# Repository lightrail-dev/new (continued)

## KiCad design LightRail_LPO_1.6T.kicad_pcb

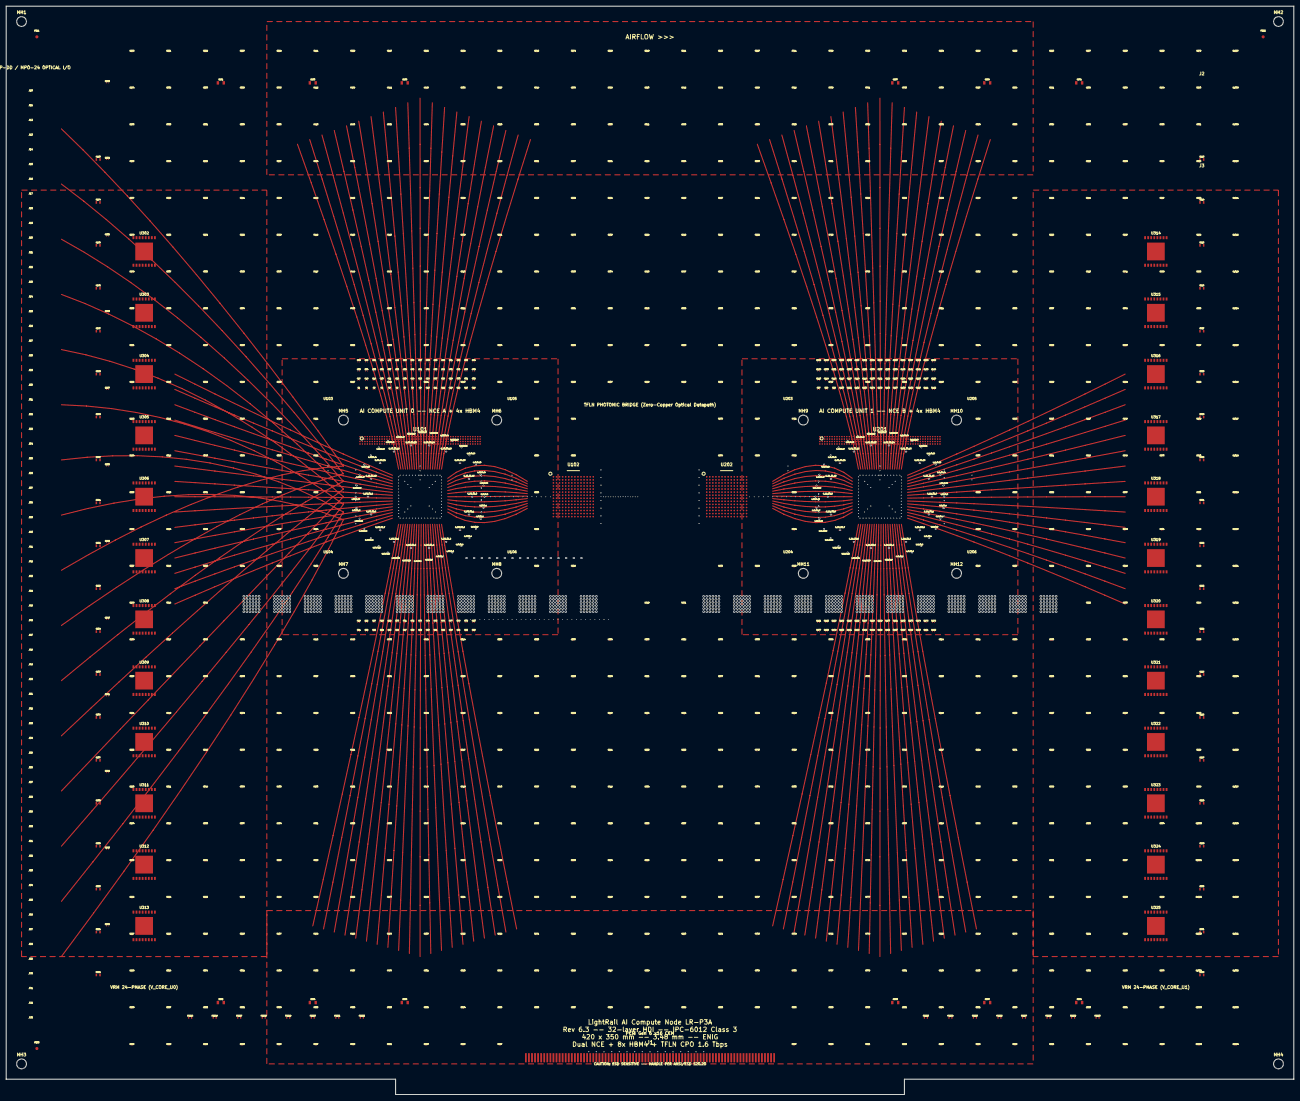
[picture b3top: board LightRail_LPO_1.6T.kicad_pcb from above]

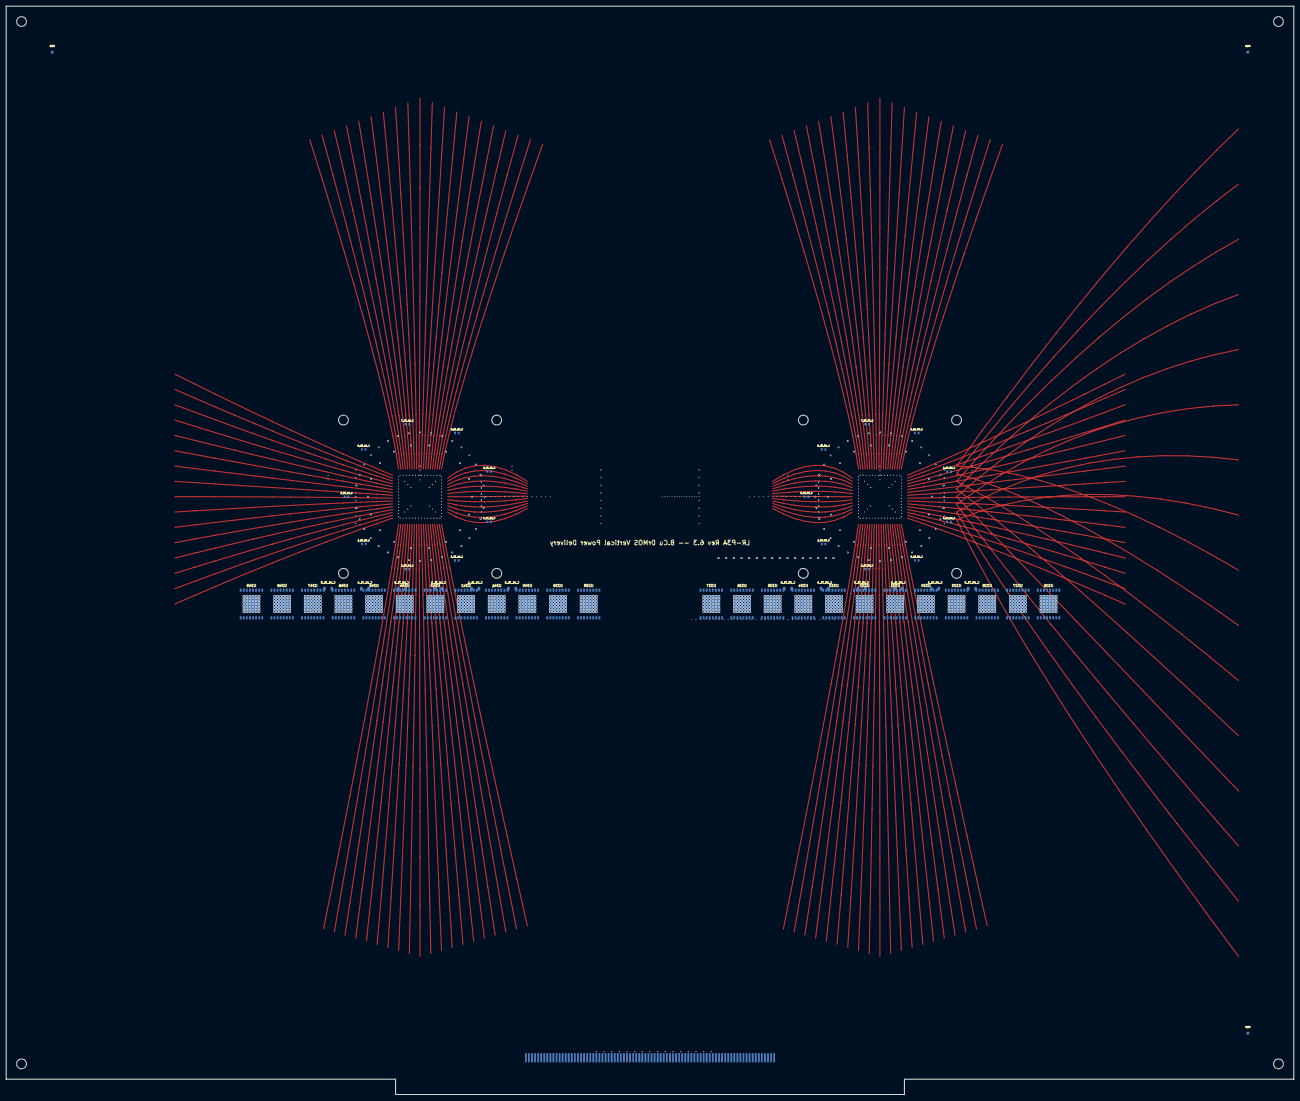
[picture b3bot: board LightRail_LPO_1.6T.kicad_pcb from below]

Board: 32 copper layers, 420.0 x 355.0 mm, 1317 parts (57 on the bottom side), 3 nets.

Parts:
C1, C2, C3, C4, C5, C6, C7, C8, C9, C10, C11, C12, C13, C14, C15, C16, C17, C18, C19, C20, C21, C22, C23, C24, C25, C26, C27, C28, C29, C30, C31, C32, C33, C34, C35, C36, C37, C38, C39, C40, C41, C42, C43, C44, C45, C46, C47, C48, C49, C50, C51, C52, C53, C54, C55, C56, C57, C58, C59, C60, C61, C62, C63, C64, C65, C66, C67, C68, C69, C70, C71, C72, C73, C74, C75, C76, C77, C78, C79, C80, C81, C82, C83, C84, C85, C86, C87, C88, C89, C90, C91, C92, C93, C94, C95, C96, C97, C98, C99, C100, C101, C102, C103, C104, C105, C106, C107, C108, C109, C110, C111, C112, C113, C114, C115, C116, C117, C118, C119, C120, C121, C122, C123, C124, C125, C126, C127, C128, C129, C130, C131, C132, C133, C134, C135, C136, C137, C138, C139, C140, C141, C142, C143, C144, C145, C146, C147, C148, C149, C150, C151, C152, C153, C154, C155, C156, C157, C158, C159, C160, C161, C162, C163, C164, C165, C166, C167, C168, C169, C170, C171, C172, C173, C174, C175, C176, C177, C178, C179, C180, C181, C182, C183, C184, C185, C186, C187, C188, C189, C190, C191, C192: 1.0x0.5; C_passive
C193, C194, C195, C196, C197, C198, C199, C200, C201, C202, C203, C204, C205, C206, C207, C208, C209, C210, C211, C212, C213, C214, C215, C216, C217, C218, C219, C220, C221, C222, C223, C224, C225, C226, C227, C228, C229, C230, C231, C232: 2.0x1.25; C_passive
C261, C262, C263, C264, C265, C266, C267, C268, C269, C270, C271, C272: 3.2x1.6; C_passive
C273, C274, C275, C276, C277, C278, C279, C280, C281, C282, C283, C284, C285, C286, C287, C288, C289, C290, C291, C292, C293, C294, C295, C296, C297, C298, C299, C300, C301, C302, C303, C304, C305, C306, C307, C308, C309, C310, C311, C312, C313, C314, C315, C316, C317, C318, C319, C320, C321, C322, C323, C324, C325, C326, C327, C328, C329, C330, C331, C332, C333, C334, C335, C336, C337, C338, C339, C340, C341, C342, C343, C344, C345, C346, C347, C348, C349, C350, C351, C352, C353, C354, C355, C356, C357, C358, C359, C360, C361, C362, C363, C364, C365, C366, C367, C368, C369, C370, C371, C372, C373, C374, C375, C376, C377, C378, C379, C380, C381, C382, C383, C384, C385, C386, C387, C388, C389, C390, C391, C392, C393, C394, C395, C396, C397, C398, C399, C400, C401, C402, C403, C404, C405, C406, C407, C408, C409, C410, C411, C412, C413, C414, C415, C416, C417, C418, C419, C420, C421, C422, C423, C424, C425, C426, C427, C428, C429, C430, C431, C432, C433, C434, C435, C436, C437, C438, C439, C440, C441, C442, C443, C444, C445, C446, C447, C448, C449, C450, C451, C452, C453, C454, C455, C456, C457, C458, C459, C460, C461, C462, C463, C464, C465, C466, C467, C468, C469, C470, C471, C472, C473, C474, C475, C476, C477, C478, C479, C480, C481, C482, C483, C484, C485, C486, C487, C488, C489, C490, C491, C492, C493, C494, C495, C496, C497, C498, C499, C500, C501, C502, C503, C504, C505, C506, C507, C508, C509, C510, C511, C512, C513, C514, C515, C516, C517, C518, C519, C520, C521, C522, C523, C524, C525, C526, C527, C528, C529, C530, C531, C532, C533, C534, C535, C536, C537, C538, C539, C540, C541, C542, C543, C544, C545, C546, C547, C548, C549, C550, C551, C552, C553, C554, C555, C556, C557, C558, C559, C560, C561, C562, C563, C564, C565, C566, C567, C568, C569, C570, C571, C572, C573, C574, C575, C576, C577, C578, C579, C580, C581, C582, C583, C584, C585, C586, C587, C588, C589, C590, C591, C592, C593, C594, C595, C596, C597, C598, C599, C600, C601, C602, C603, C604, C605, C606, C607, C608, C609, C610, C611, C612, C613, C614, C615, C616, C617, C618, C619, C620, C621, C622, C623, C624, C625, C626, C627, C628, C629, C630, C631, C632, C633, C634, C635, C636, C637, C638, C639, C640, C641, C642, C643, C644, C645, C646, C647, C648, C649, C650, C651, C652, C653, C654, C655, C656, C657, C658, C659, C660, C661, C662, C663, C664, C665, C666, C667, C668, C669, C670, C671, C672, C673, C674, C675, C676, C677, C678, C679, C680, C681, C682, C683, C684, C685, C686, C687, C688, C689, C690, C691, C692, C693, C694, C695, C696, C697, C698, C699, C700, C701, C702, C703, C704, C705, C706, C707, C708, C709, C710, C711, C712, C713, C714, C715, C716, C717, C718, C719, C720, C721, C722, C723, C724, C725, C726, C727, C728, C729, C730, C731, C732, C733, C734, C735, C736, C737, C738, C739, C740, C741, C742, C743, C744, C745, C746, C747, C748, C749, C750, C751, C752, C753, C754, C755, C756, C757, C758, C759, C760, C761, C762, C763, C764, C765, C766, C767, C768, C769, C770, C771, C772, C773, C774, C775, C776, C777, C778, C779, C780, C781, C782, C783, C784, C785, C786, C787, C788, C789, C790, C791, C792, C793, C794, C795, C796, C797, C798, C799, C800, C801, C802, C803, C804, C805, C806, C807, C808, C809, C810, C811, C812, C813, C814, C815, C816, C817, C818, C819, C820, C821, C822, C823, C824, C825, C826, C827, C828, C829, C830, C831, C832, C833, C834, C835, C836, C837, C838, C839, C840, C841, C842, C843, C844, C845, C846, C847, C848, C849, C850, C851, C852, C853, C854, C855, C856, C857, C858, C859, C860, C861, C862, C863, C864, C865, C866, C867, C868, C869, C870, C871, C872, C873, C874, C875, C876, C877, C878, C879, C880, C881, C882, C883, C884, C885, C886, C887, C888, C889, C890, C891, C892, C893, C894, C895, C896, C897, C898, C899, C900, C901, C902, C903, C904, C905, C906, C907, C908, C909, C910, C911, C912, C913, C914, C915, C916, C917, C918, C919, C920, C921, C922, C923, C924, C925, C926, C927, C928, C929, C930, C931, C932, C933, C934, C935, C936, C937, C938, C939, C940, C941, C942, C943, C944, C945, C946, C947, C948, C949, C950, C951, C952, C953, C954, C955, C956, C957, C958, C959, C960, C961, C962, C963, C964, C965, C966, C967, C968, C969, C970, C971, C972, C973, C974, C975, C976, C977, C978, C979, C980, C981, C982, C983, C984, C985, C986, C987, C988, C989, C990, C991, C992, C993, C994, C995, C996, C997, C998, C999, C1000, C1001, C1002, C1003, C1004, C1005, C1006, C1007, C1008, C1009, C1010, C1011, C1012, C1013, C1014, C1015, C1016, C1017, C1018, C1019, C1020, C1021, C1022, C1023, C1024, C1025, C1026, C1027, C1028, C1029, C1030, C1031, C1032, C1033, C1034: 0.6x0.3; C_passive
C_U0_T1_0, C_U0_T1_1, C_U0_T1_2, C_U0_T1_3, C_U0_T1_4, C_U0_T1_5, C_U1_T1_0, C_U1_T1_1, C_U1_T1_2, C_U1_T1_3, C_U1_T1_4, C_U1_T1_5: 100uF_10V; C_Tantalum_3528
C_U0_T2_0, C_U0_T2_1, C_U0_T2_2, C_U0_T2_3, C_U0_T2_4, C_U0_T2_5, C_U0_T2_6, C_U0_T2_7, C_U0_T2_8, C_U1_T2_0, C_U1_T2_1, C_U1_T2_2, C_U1_T2_3, C_U1_T2_4, C_U1_T2_5, C_U1_T2_6, C_U1_T2_7, C_U1_T2_8: 10uF; C_0805
C_U0_T3_0, C_U0_T3_1, C_U0_T3_2, C_U0_T3_3, C_U0_T3_4, C_U0_T3_5, C_U0_T3_6, C_U0_T3_7, C_U0_T3_8, C_U0_T3_9, C_U0_T3_10, C_U0_T3_11, C_U0_T3_12, C_U0_T3_13, C_U0_T3_14, C_U0_T3_15, C_U0_T3_16, C_U0_T3_17, C_U1_T3_0, C_U1_T3_1, C_U1_T3_2, C_U1_T3_3, C_U1_T3_4, C_U1_T3_5, C_U1_T3_6, C_U1_T3_7, C_U1_T3_8, C_U1_T3_9, C_U1_T3_10, C_U1_T3_11, C_U1_T3_12, C_U1_T3_13, C_U1_T3_14, C_U1_T3_15, C_U1_T3_16, C_U1_T3_17: 1uF; C_0402
C_U0_T4_0, C_U0_T4_1, C_U0_T4_2, C_U0_T4_3, C_U0_T4_4, C_U0_T4_5, C_U0_T4_6, C_U0_T4_7, C_U0_T4_8, C_U0_T4_9, C_U0_T4_10, C_U0_T4_11, C_U0_T4_12, C_U0_T4_13, C_U0_T4_14, C_U0_T4_15, C_U0_T4_16, C_U0_T4_17, C_U0_T4_18, C_U0_T4_19, C_U0_T4_20, C_U0_T4_21, C_U0_T4_22, C_U0_T4_23, C_U0_T4_24, C_U0_T4_25, C_U0_T4_26, C_U0_T4_27, C_U0_T4_28, C_U0_T4_29, C_U0_T4_30, C_U0_T4_31, C_U0_T4_32, C_U0_T4_33, C_U0_T4_34, C_U0_T4_35, C_U1_T4_0, C_U1_T4_1, C_U1_T4_2, C_U1_T4_3, C_U1_T4_4, C_U1_T4_5, C_U1_T4_6, C_U1_T4_7, C_U1_T4_8, C_U1_T4_9, C_U1_T4_10, C_U1_T4_11, C_U1_T4_12, C_U1_T4_13, C_U1_T4_14, C_U1_T4_15, C_U1_T4_16, C_U1_T4_17, C_U1_T4_18, C_U1_T4_19, C_U1_T4_20, C_U1_T4_21, C_U1_T4_22, C_U1_T4_23, C_U1_T4_24, C_U1_T4_25, C_U1_T4_26, C_U1_T4_27, C_U1_T4_28, C_U1_T4_29, C_U1_T4_30, C_U1_T4_31, C_U1_T4_32, C_U1_T4_33, C_U1_T4_34, C_U1_T4_35: 100nF; C_01005
FB245, FB246, FB247, FB248, FB249, FB250, FB251, FB252, FB253, FB254, FB255, FB256, FB257, FB258, FB259, FB260: 1.6x0.8; FB_passive
FID1, FID2, FID3, FID4, FID5, FID6: Fiducial; Fiducial_1mm_Mask2.5mm
J1: PCIe_Gen6_x16_CEM; PCIe_CEM_x16_164pin
J2, J3: 12VHPWR_600W; 12VHPWR_Molex_203713
J10, J11, J12, J13, J14, J15, J16, J17, J18, J19, J20, J21, J22, J23, J24, J25, J26, J27, J28, J29, J30, J31, J32, J33, J34, J35, J36, J37, J38, J39, J40, J41, J42, J43, J44, J45, J46, J47, J48, J49, J50, J51, J52, J53, J54, J55, J56, J57, J58, J59, J60, J61, J62, J63, J64, J65, J66, J67, J68, J69, J70, J71, J72, J73: QSFP-DD; QSFP_DD_Cage
MH1, MH2, MH3, MH4, MH5, MH6, MH7, MH8, MH9, MH10, MH11, MH12: MountingHole; MountingHole_3.2mm_M3
R233, R234, R235, R236, R237, R238, R239, R240, R241, R242, R243, R244: 1.0x0.5; R_passive
U101, U201: NCE_BGA2500_HBM4; NCE_BGA2500_40x40mm
U102, U202: TFLN_PIC_8CH_200G; TFLN_PIC_17x17mm
U103, U104, U105, U106, U203, U204, U205, U206: HBM4_12Hi_48GB; HBM4_Stack_11x11mm
U302, U303, U304, U305, U306, U307, U308, U309, U310, U311, U312, U313, U314, U315, U316, U317, U318, U319, U320, U321, U322, U323, U324, U325, U326, U327, U328, U329, U330, U331, U332, U333, U334, U335, U336, U337, U338, U339, U340, U341, U342, U343, U344, U345, U346, U347, U348, U349: ISL99390; DrMOS_PowerPAK_8x8mm

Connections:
GND: C_U0_T1_0.2, C_U0_T1_1.2, C_U0_T1_2.2, C_U0_T1_3.2, C_U0_T1_4.2, C_U0_T1_5.2, C_U0_T2_0.2, C_U0_T2_1.2, C_U0_T2_2.2, C_U0_T2_3.2, C_U0_T2_4.2, C_U0_T2_5.2, C_U0_T2_6.2, C_U0_T2_7.2, C_U0_T2_8.2, C_U0_T3_0.2, C_U0_T3_1.2, C_U0_T3_2.2, C_U0_T3_3.2, C_U0_T3_4.2, C_U0_T3_5.2, C_U0_T3_6.2, C_U0_T3_7.2, C_U0_T3_8.2, C_U0_T3_9.2, C_U0_T3_10.2, C_U0_T3_11.2, C_U0_T3_12.2, C_U0_T3_13.2, C_U0_T3_14.2, C_U0_T3_15.2, C_U0_T3_16.2, C_U0_T3_17.2, C_U0_T4_0.2, C_U0_T4_1.2, C_U0_T4_2.2, C_U0_T4_3.2, C_U0_T4_4.2, C_U0_T4_5.2, C_U0_T4_6.2, C_U0_T4_7.2, C_U0_T4_8.2, C_U0_T4_9.2, C_U0_T4_10.2, C_U0_T4_11.2, C_U0_T4_12.2, C_U0_T4_13.2, C_U0_T4_14.2, C_U0_T4_15.2, C_U0_T4_16.2, C_U0_T4_17.2, C_U0_T4_18.2, C_U0_T4_19.2, C_U0_T4_20.2, C_U0_T4_21.2, C_U0_T4_22.2, C_U0_T4_23.2, C_U0_T4_24.2, C_U0_T4_25.2, C_U0_T4_26.2, C_U0_T4_27.2, C_U0_T4_28.2, C_U0_T4_29.2, C_U0_T4_30.2, C_U0_T4_31.2, C_U0_T4_32.2, C_U0_T4_33.2, C_U0_T4_34.2, C_U0_T4_35.2, C_U1_T1_0.2, C_U1_T1_1.2, C_U1_T1_2.2, C_U1_T1_3.2, C_U1_T1_4.2, C_U1_T1_5.2, C_U1_T2_0.2, C_U1_T2_1.2, C_U1_T2_2.2, C_U1_T2_3.2, C_U1_T2_4.2, C_U1_T2_5.2, C_U1_T2_6.2, C_U1_T2_7.2, C_U1_T2_8.2, C_U1_T3_0.2, C_U1_T3_1.2, C_U1_T3_2.2, C_U1_T3_3.2, C_U1_T3_4.2, C_U1_T3_5.2, C_U1_T3_6.2, C_U1_T3_7.2, C_U1_T3_8.2, C_U1_T3_9.2, C_U1_T3_10.2, C_U1_T3_11.2, C_U1_T3_12.2, C_U1_T3_13.2, C_U1_T3_14.2, C_U1_T3_15.2, C_U1_T3_16.2, C_U1_T3_17.2, C_U1_T4_0.2, C_U1_T4_1.2, C_U1_T4_2.2, C_U1_T4_3.2, C_U1_T4_4.2, C_U1_T4_5.2, C_U1_T4_6.2, C_U1_T4_7.2, C_U1_T4_8.2, C_U1_T4_9.2, C_U1_T4_10.2, C_U1_T4_11.2, C_U1_T4_12.2, C_U1_T4_13.2, C_U1_T4_14.2, C_U1_T4_15.2, C_U1_T4_16.2, C_U1_T4_17.2, C_U1_T4_18.2, C_U1_T4_19.2, C_U1_T4_20.2, C_U1_T4_21.2, C_U1_T4_22.2, C_U1_T4_23.2, C_U1_T4_24.2, C_U1_T4_25.2, C_U1_T4_26.2, C_U1_T4_27.2, C_U1_T4_28.2, C_U1_T4_29.2, C_U1_T4_30.2, C_U1_T4_31.2, C_U1_T4_32.2, C_U1_T4_33.2, C_U1_T4_34.2, C_U1_T4_35.2, J1.A1, J1.A2, J1.A3, J1.A4, J1.A5, J1.A6, J1.A7, J1.A8, J1.A9, J1.A10, J1.A11, J1.A12, J1.A13, J1.A14, J1.A15, J1.A16, J1.A17, J1.A18, J1.A19, J1.A20, J1.A21, J1.A22, J1.A23, J1.A24, J1.A25, J1.A26, J1.A27, J1.A28, J1.A29, J1.A30, J1.A31, J1.A32, J1.A33, J1.A34, J1.A35, J1.A36, J1.A37, J1.A38, J1.A39, J1.A40, J1.A41, J1.A42, J1.A43, J1.A44, J1.A45, J1.A46, J1.A47, J1.A48, J1.A49, J1.A50, J1.A51, J1.A52, J1.A53, J1.A54, J1.A55, J1.A56, J1.A57, J1.A58, J1.A59, J1.A60, J1.A61, J1.A62, J1.A63, J1.A64, J1.A65, J1.A66, J1.A67, J1.A68, J1.A69, J1.A70, J1.A71, J1.A72, J1.A73, J1.A74, J1.A75, J1.A76, J1.A77, J1.A78, J1.A79, J1.A80, J1.A81, J1.A82, J1.B1, J1.B2, J1.B3, J1.B4, J1.B5, J1.B6, J1.B7, J1.B8, J1.B9, J1.B10, J1.B11, J1.B12, J1.B13, J1.B14, J1.B15, J1.B16, J1.B17, J1.B18, J1.B19, J1.B20, J1.B21, J1.B22, J1.B23, J1.B24, J1.B25, J1.B26, J1.B27, J1.B28, J1.B29, J1.B30, J1.B31, J1.B32, J1.B33, J1.B34, J1.B35, J1.B36, J1.B37, J1.B38, J1.B39, J1.B40, J1.B41, J1.B42, J1.B43, J1.B44, J1.B45, J1.B46, J1.B47, J1.B48, J1.B49, J1.B50, J1.B51, J1.B52, J1.B53, J1.B54, J1.B55, J1.B56, J1.B57, J1.B58, J1.B59, J1.B60, J1.B61, J1.B62, J1.B63, J1.B64, J1.B65, J1.B66, J1.B67, J1.B68, J1.B69, J1.B70, J1.B71, J1.B72, J1.B73, J1.B74, J1.B75, J1.B76, J1.B77, J1.B78, J1.B79, J1.B80, J1.B81, J1.B82, U101.A1, U101.A3, U101.A5, U101.A7, U101.A9, U101.A11, U101.A13, U101.A15, U101.A17, U101.A19, U101.A21, U101.A23, U101.A25, U101.A27, U101.A29, U101.A31, U101.A33, U101.A35, U101.A37, U101.A39, U101.A41, U101.A43, U101.A45, U101.A47, U101.A49, U101.B2, U101.B4, U101.B6, U101.B8, U101.B10, U101.B12, U101.B14, U101.B16, U101.B18, U101.B20, U101.B22, U101.B24, U101.B26, U101.B28, U101.B30, U101.B32, U101.B34, U101.B36, U101.B38, U101.B40, U101.B42, U101.B44, U101.B46, U101.B48, U101.B50, U101.C1, U101.C3, U101.C5, U101.C7, U101.C9, U101.C11, U101.C13, U101.C15, U101.C17, U101.C19, U101.C21, U101.C23, U101.C25, U101.C27, U101.C29, U101.C31, U101.C33, U101.C35, U101.C37, U101.C39, U101.C41, U101.C43, U101.C45, U101.C47, U101.C49, U101.D2, U101.D4, U101.D5, U101.D6, U101.D7, U101.D8, U101.D9, U101.D10, U101.D11, U101.D12, U101.D13, U101.D14, U101.D15, U101.D16, U101.D17, U101.D18, U101.D19, U101.D20, U101.D21, U101.D22, U101.D23, U101.D24, U101.D25, U101.D26, U101.D27, U101.D28, U101.D29, U101.D30, U101.D31, U101.D32, U101.D33, U101.D34, U101.D35, U101.D36, U101.D37, U101.D38, U101.D39, U101.D40, U101.D41, U101.D42, U101.D43, U101.D44, U101.D45, U101.D46, U101.D47, U101.D48, U101.D50, U102.A1, U102.A2, U102.A3, U102.A4, U102.A5, U102.A6, U102.A7, U102.A8, U102.A9, U102.A10, U102.A11, U102.A12, U102.A13, U102.A14, U102.B1, U102.B2, U102.B3, U102.B4, U102.B5, U102.B6, U102.B7, U102.B8, U102.B9, U102.B10, U102.B11, U102.B12, U102.B13, U102.B14, U102.C1, U102.C2, U102.C3, U102.C4, U102.C5, U102.C6, U102.C7, U102.C8, U102.C9, U102.C10, U102.C11, U102.C12, U102.C13, U102.C14, U102.D1, U102.D2, U102.D3, U102.D4, U102.D5, U102.D6, U102.D7, U102.D8, U102.D9, U102.D10, U102.D11, U102.D12, U102.D13, U102.D14, U102.E1, U102.E2, U102.E3, U102.E4, U102.E5, U102.E6, U102.E7, U102.E8, U102.E9, U102.E10, U102.E11, U102.E12, U102.E13, U102.E14, U102.F1, U102.F2, U102.F3, U102.F4, U102.F5, U102.F6, U102.F7, U102.F8, U102.F9, U102.F10, U102.F11, U102.F12, U102.F13, U102.F14, U102.G1, U102.G2, U102.G3, U102.G4, U102.G5, U102.G6, U102.G7, U102.G8, U102.G9, U102.G10, U102.G11, U102.G12, U102.G13, U102.G14, U102.H1, U102.H2, U102.H3, U102.H4, U102.H5, U102.H6, U102.H7, U102.H8, U102.H9, U102.H10, U102.H11, U102.H12, U102.H13, U102.H14, U102.I1, U102.I2, U102.I3, U102.I4, U102.I5, U102.I6, U102.I7, U102.I8, U102.I9, U102.I10, U102.I11, U102.I12, U102.I13, U102.I14, U102.J1, U102.J2, U102.J3, U102.J4, U102.J5, U102.J6, U102.J7, U102.J8, U102.J9, U102.J10, U102.J11, U102.J12, U102.J13, U102.J14, U102.K1, U102.K2, U102.K3, U102.K4, U102.K5, U102.K6, U102.K7, U102.K8, U102.K9, U102.K10, U102.K11, U102.K12, U102.K13, U102.K14, U102.L1, U102.L2, U102.L3, U102.L4, U102.L5, U102.L6, U102.L7, U102.L8, U102.L9, U102.L10, U102.L11, U102.L12, U102.L13, U102.L14, U102.M1, U102.M2, U102.M3, U102.M4, U102.M5, U102.M6, U102.M7, U102.M8, U102.M9, U102.M10, U102.M11, U102.M12, U102.M13, U102.M14, U102.N1, U102.N2, U102.N3, U102.N4, U102.N5, U102.N6, U102.N7, U102.N8, U102.N9, U102.N10, U102.N11, U102.N12, U102.N13, U102.N14, U201.A1, U201.A3, U201.A5, U201.A7, U201.A9, U201.A11, U201.A13, U201.A15, U201.A17, U201.A19, U201.A21, U201.A23, U201.A25, U201.A27, U201.A29, U201.A31, U201.A33, U201.A35, U201.A37, U201.A39, U201.A41, U201.A43, U201.A45, U201.A47, U201.A49, U201.B2, U201.B4, U201.B6, U201.B8, U201.B10, U201.B12, U201.B14, U201.B16, U201.B18, U201.B20, U201.B22, U201.B24, U201.B26, U201.B28, U201.B30, U201.B32, U201.B34, U201.B36, U201.B38, U201.B40, U201.B42, U201.B44, U201.B46, U201.B48, U201.B50, U201.C1, U201.C3, U201.C5, U201.C7, U201.C9, U201.C11, U201.C13, U201.C15, U201.C17, U201.C19, U201.C21, U201.C23, U201.C25, U201.C27, U201.C29, U201.C31, U201.C33, U201.C35, U201.C37, U201.C39, U201.C41, U201.C43, U201.C45, U201.C47, U201.C49, U201.D2, U201.D4, U201.D5, U201.D6, U201.D7, U201.D8, U201.D9, U201.D10, U201.D11, U201.D12, U201.D13, U201.D14, U201.D15, U201.D16, U201.D17, U201.D18, U201.D19, U201.D20, U201.D21, U201.D22, U201.D23, U201.D24, U201.D25, U201.D26, U201.D27, U201.D28, U201.D29, U201.D30, U201.D31, U201.D32, U201.D33, U201.D34, U201.D35, U201.D36, U201.D37, U201.D38, U201.D39, U201.D40, U201.D41, U201.D42, U201.D43, U201.D44, U201.D45, U201.D46, U201.D47, U201.D48, U201.D50, U202.A1, U202.A2, U202.A3, U202.A4, U202.A5, U202.A6, U202.A7, U202.A8, U202.A9, U202.A10, U202.A11, U202.A12, U202.A13, U202.A14, U202.B1, U202.B2, U202.B3, U202.B4, U202.B5, U202.B6, U202.B7, U202.B8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
V_CORE_U0: U101.A2, U101.A4, U101.A6, U101.A8, U101.A10, U101.A12, U101.A14, U101.A16, U101.A18, U101.A20, U101.A22, U101.A24, U101.A26, U101.A28, U101.A30, U101.A32, U101.A34, U101.A36, U101.A38, U101.A40, U101.A42, U101.A44, U101.A46, U101.A48, U101.A50, U101.B1, U101.B3, U101.B5, U101.B7, U101.B9, U101.B11, U101.B13, U101.B15, U101.B17, U101.B19, U101.B21, U101.B23, U101.B25, U101.B27, U101.B29, U101.B31, U101.B33, U101.B35, U101.B37, U101.B39, U101.B41, U101.B43, U101.B45, U101.B47, U101.B49, U101.C2, U101.C4, U101.C6, U101.C8, U101.C10, U101.C12, U101.C14, U101.C16, U101.C18, U101.C20, U101.C22, U101.C24, U101.C26, U101.C28, U101.C30, U101.C32, U101.C34, U101.C36, U101.C38, U101.C40, U101.C42, U101.C44, U101.C46, U101.C48, U101.C50, U101.D1, U101.D3, U101.D49, U302.EP, U303.EP, U304.EP, U305.EP, U306.EP, U307.EP, U308.EP, U309.EP, U310.EP, U311.EP, U312.EP, U313.EP, U326.EP, U327.EP, U328.EP, U329.EP, U330.EP, U331.EP, U332.EP, U333.EP, U334.EP, U335.EP, U336.EP, U337.EP
V_CORE_U1: U201.A2, U201.A4, U201.A6, U201.A8, U201.A10, U201.A12, U201.A14, U201.A16, U201.A18, U201.A20, U201.A22, U201.A24, U201.A26, U201.A28, U201.A30, U201.A32, U201.A34, U201.A36, U201.A38, U201.A40, U201.A42, U201.A44, U201.A46, U201.A48, U201.A50, U201.B1, U201.B3, U201.B5, U201.B7, U201.B9, U201.B11, U201.B13, U201.B15, U201.B17, U201.B19, U201.B21, U201.B23, U201.B25, U201.B27, U201.B29, U201.B31, U201.B33, U201.B35, U201.B37, U201.B39, U201.B41, U201.B43, U201.B45, U201.B47, U201.B49, U201.C2, U201.C4, U201.C6, U201.C8, U201.C10, U201.C12, U201.C14, U201.C16, U201.C18, U201.C20, U201.C22, U201.C24, U201.C26, U201.C28, U201.C30, U201.C32, U201.C34, U201.C36, U201.C38, U201.C40, U201.C42, U201.C44, U201.C46, U201.C48, U201.C50, U201.D1, U201.D3, U201.D49, U314.EP, U315.EP, U316.EP, U317.EP, U318.EP, U319.EP, U320.EP, U321.EP, U322.EP, U323.EP, U324.EP, U325.EP, U338.EP, U339.EP, U340.EP, U341.EP, U342.EP, U343.EP, U344.EP, U345.EP, U346.EP, U347.EP, U348.EP, U349.EP

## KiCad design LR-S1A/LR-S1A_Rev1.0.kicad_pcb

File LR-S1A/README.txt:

LR-S1A 1U CPO Switch Motherboard — Rev 1.0 Manufacturing Release
================================================================

Date: 2026-04-19
Designer: LightRail AI — Design Automation
Format: KiCad 8 native (schema 20240108)
Outline: 440 x 550 mm 1U rack-mount motherboard
Stackup: 18-layer HDI (Megtron-7 / High-Tg FR-4 / Faradflex BC24)

Directory layout
----------------
  native/      KiCad 8 project (.kicad_pcb / .kicad_pro)
  gerbers/     RS-274X Gerber 27 layers (18 Cu + masks/silks/paste/fab/edge)
  drill/       Excellon 2.0 PTH + NPTH
  3d/          STEP AP242 board outline + components
  ipc2581/     IPC-2581 Rev C unified design exchange package
  pdfs/        27 per-layer PDFs (A2 landscape, with plane fill + antipads
               + characteristics + compliance summary for each layer)
  drawings/    Fab Drawing, Assembly Drawings (top + bottom), Layer Index
               — all A2 landscape, full title block, IPC-grade content
  BOM.csv      2,320-part architectural BOM (5 categories)
  *_pnp.csv    Pick-and-place CSV (both sides, mm)
  DRC_report.rpt   IPC-6012 Class 3 DRC sign-off: 0 errors

DRC: IPC-6012 Class 3 ruleset, 0 violations.

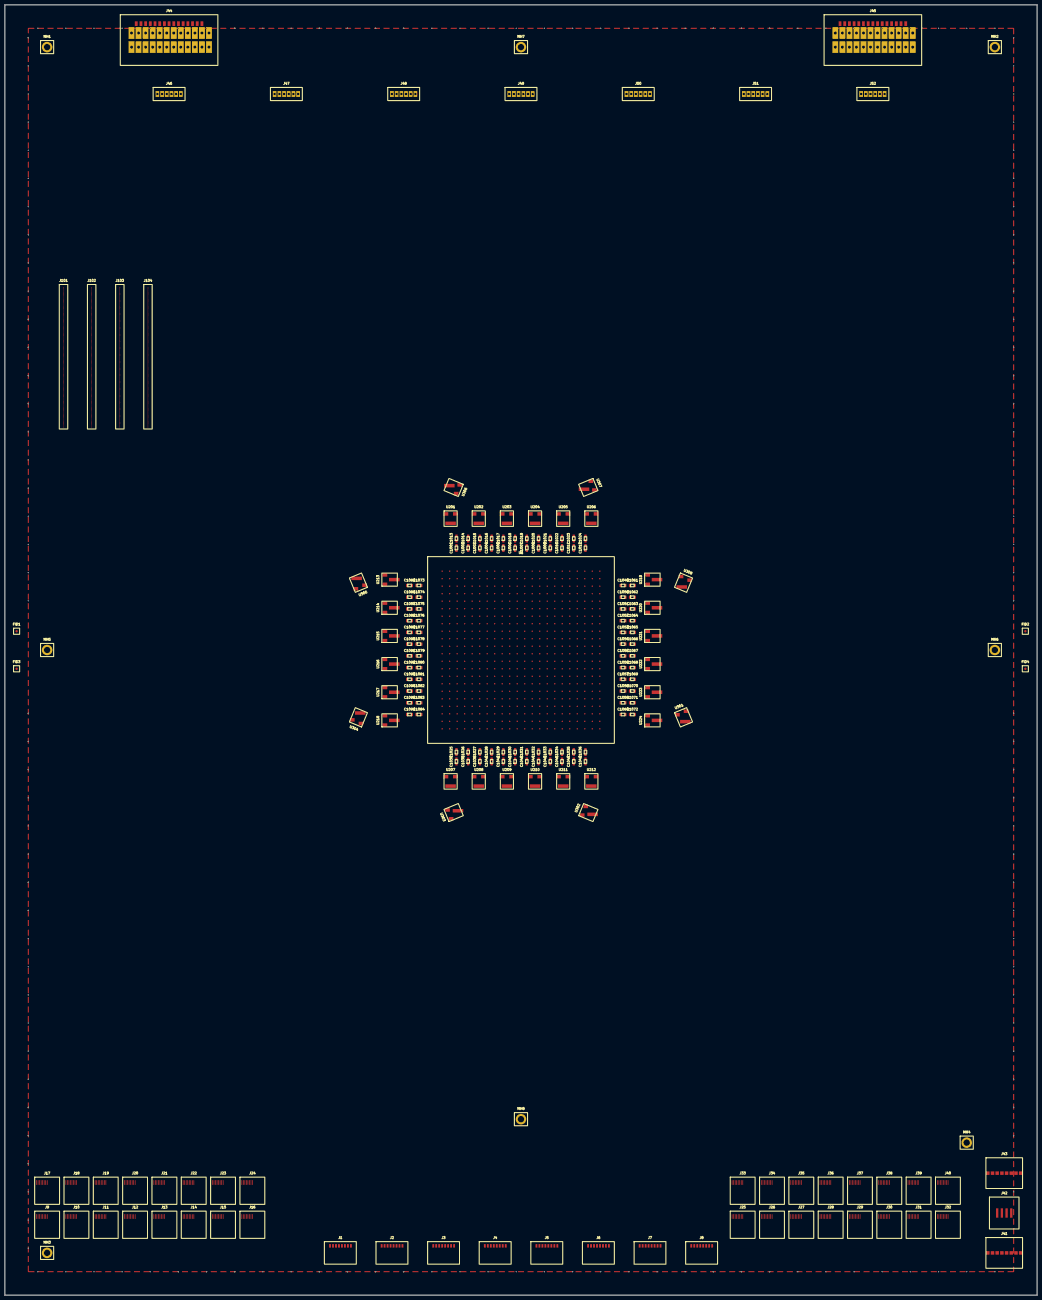
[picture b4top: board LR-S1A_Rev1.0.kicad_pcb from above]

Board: 18 copper layers, 440.0 x 550.0 mm, 197 parts (0 on the bottom side), 48 nets, no tracks yet.

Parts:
C1001, C1002, C1003, C1004, C1005, C1006, C1007, C1008, C1009, C1010, C1011, C1012, C1013, C1014, C1015, C1016, C1017, C1018, C1019, C1020, C1021, C1022, C1023, C1024, C1025, C1026, C1027, C1028, C1029, C1030, C1031, C1032, C1033, C1034, C1035, C1036, C1037, C1038, C1039, C1040, C1041, C1042, C1043, C1044, C1045, C1046, C1047, C1048, C1049, C1050, C1051, C1052, C1053, C1054, C1055, C1056, C1057, C1058, C1059, C1060, C1061, C1062, C1063, C1064, C1065, C1066, C1067, C1068, C1069, C1070, C1071, C1072, C1073, C1074, C1075, C1076, C1077, C1078, C1079, C1080, C1081, C1082, C1083, C1084, C1085, C1086, C1087, C1088, C1089, C1090, C1091, C1092, C1093, C1094, C1095, C1096: 10uF; Cap_0805_2012Metric
FID1, FID2, FID3, FID4: Fiducial 1mm/2mm; Fiducial_1mm
J1: ELSFP CW Laser Cage #1; ELSFP_Cage_SFP-DD
J2: ELSFP CW Laser Cage #2; ELSFP_Cage_SFP-DD
J3: ELSFP CW Laser Cage #3; ELSFP_Cage_SFP-DD
J4: ELSFP CW Laser Cage #4; ELSFP_Cage_SFP-DD
J5: ELSFP CW Laser Cage #5; ELSFP_Cage_SFP-DD
J6: ELSFP CW Laser Cage #6; ELSFP_Cage_SFP-DD
J7: ELSFP CW Laser Cage #7; ELSFP_Cage_SFP-DD
J8: ELSFP CW Laser Cage #8; ELSFP_Cage_SFP-DD
J9: OSFP-XD Port #1 (left lower); OSFP-XD_Cage
J10: OSFP-XD Port #2 (left lower); OSFP-XD_Cage
J11: OSFP-XD Port #3 (left lower); OSFP-XD_Cage
J12: OSFP-XD Port #4 (left lower); OSFP-XD_Cage
J13: OSFP-XD Port #5 (left lower); OSFP-XD_Cage
J14: OSFP-XD Port #6 (left lower); OSFP-XD_Cage
J15: OSFP-XD Port #7 (left lower); OSFP-XD_Cage
J16: OSFP-XD Port #8 (left lower); OSFP-XD_Cage
J17: OSFP-XD Port #9 (left upper); OSFP-XD_Cage
J18: OSFP-XD Port #10 (left upper); OSFP-XD_Cage
J19: OSFP-XD Port #11 (left upper); OSFP-XD_Cage
J20: OSFP-XD Port #12 (left upper); OSFP-XD_Cage
J21: OSFP-XD Port #13 (left upper); OSFP-XD_Cage
J22: OSFP-XD Port #14 (left upper); OSFP-XD_Cage
J23: OSFP-XD Port #15 (left upper); OSFP-XD_Cage
J24: OSFP-XD Port #16 (left upper); OSFP-XD_Cage
J25: OSFP-XD Port #17 (right lower); OSFP-XD_Cage
J26: OSFP-XD Port #18 (right lower); OSFP-XD_Cage
J27: OSFP-XD Port #19 (right lower); OSFP-XD_Cage
J28: OSFP-XD Port #20 (right lower); OSFP-XD_Cage
J29: OSFP-XD Port #21 (right lower); OSFP-XD_Cage
J30: OSFP-XD Port #22 (right lower); OSFP-XD_Cage
J31: OSFP-XD Port #23 (right lower); OSFP-XD_Cage
J32: OSFP-XD Port #24 (right lower); OSFP-XD_Cage
J33: OSFP-XD Port #25 (right upper); OSFP-XD_Cage
J34: OSFP-XD Port #26 (right upper); OSFP-XD_Cage
J35: OSFP-XD Port #27 (right upper); OSFP-XD_Cage
J36: OSFP-XD Port #28 (right upper); OSFP-XD_Cage
J37: OSFP-XD Port #29 (right upper); OSFP-XD_Cage
J38: OSFP-XD Port #30 (right upper); OSFP-XD_Cage
J39: OSFP-XD Port #31 (right upper); OSFP-XD_Cage
J40: OSFP-XD Port #32 (right upper); OSFP-XD_Cage
J41: RJ-45 OOB Management 1 GbE; RJ-45_Bel_MagJack
J42: USB-A Type-A Console; USB_A_Type-A
J43: RJ-45 RS-232 Console; RJ-45_Console
J44: CRPS-1U PSU Connector A (3 kW Titanium); CRPS_1U_Power
J45: CRPS-1U PSU Connector B (3 kW Titanium); CRPS_1U_Power
J46: Fan Header #1 (Sanyo Denki San Ace 40); Fan_Header_6pin
J47: Fan Header #2 (Sanyo Denki San Ace 40); Fan_Header_6pin
J48: Fan Header #3 (Sanyo Denki San Ace 40); Fan_Header_6pin
J49: Fan Header #4 (Sanyo Denki San Ace 40); Fan_Header_6pin
J50: Fan Header #5 (Sanyo Denki San Ace 40); Fan_Header_6pin
J51: Fan Header #6 (Sanyo Denki San Ace 40); Fan_Header_6pin
J52: Fan Header #7 (Sanyo Denki San Ace 40); Fan_Header_6pin
J101: Samtec ARC-200 (strip 1/4); Samtec_ARC_200
J102: Samtec ARC-200 (strip 2/4); Samtec_ARC_200
J103: Samtec ARC-200 (strip 3/4); Samtec_ARC_200
J104: Samtec ARC-200 (strip 4/4); Samtec_ARC_200
MH1, MH2, MH3, MH4, MH5, MH6, MH7, MH8: M2.5 PEM Standoff; MountingHole_M2.5_PEM
U1: LR-CSW-51T2 ASIC + 16x CPO engines (composite); LR-CSW-51T2_Composite_80x80
U201, U202, U203, U204, U205, U206, U207, U208, U209, U210, U211, U212, U213, U214, U215, U216, U217, U218, U219, U220, U221, U222, U223, U224, U301, U302, U303, U304, U305, U306, U307, U308: MPS MP86957 DrMOS 70A; MPS_MP86957_QFN44_5x6

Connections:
CONSOLE_TX: J43.1, J43.2, J43.3, J43.4, J43.5, J43.6, J43.7, J43.8
DB_CTL_00: J101.1, J101.33, J101.65, J101.97, J102.1, J102.33, J102.65, J102.97, J103.1, J103.33, J103.65, J103.97, J104.1, J104.33, J104.65, J104.97
DB_CTL_01: J101.2, J101.34, J101.66, J101.98, J102.2, J102.34, J102.66, J102.98, J103.2, J103.34, J103.66, J103.98, J104.2, J104.34, J104.66, J104.98
DB_CTL_02: J101.3, J101.35, J101.67, J101.99, J102.3, J102.35, J102.67, J102.99, J103.3, J103.35, J103.67, J103.99, J104.3, J104.35, J104.67, J104.99
DB_CTL_03: J101.4, J101.36, J101.68, J101.100, J102.4, J102.36, J102.68, J102.100, J103.4, J103.36, J103.68, J103.100, J104.4, J104.36, J104.68, J104.100
DB_CTL_04: J101.5, J101.37, J101.69, J101.101, J102.5, J102.37, J102.69, J102.101, J103.5, J103.37, J103.69, J103.101, J104.5, J104.37, J104.69, J104.101
DB_CTL_05: J101.6, J101.38, J101.70, J101.102, J102.6, J102.38, J102.70, J102.102, J103.6, J103.38, J103.70, J103.102, J104.6, J104.38, J104.70, J104.102
DB_CTL_06: J101.7, J101.39, J101.71, J101.103, J102.7, J102.39, J102.71, J102.103, J103.7, J103.39, J103.71, J103.103, J104.7, J104.39, J104.71, J104.103
DB_CTL_07: J101.8, J101.40, J101.72, J101.104, J102.8, J102.40, J102.72, J102.104, J103.8, J103.40, J103.72, J103.104, J104.8, J104.40, J104.72, J104.104
DB_CTL_08: J101.9, J101.41, J101.73, J101.105, J102.9, J102.41, J102.73, J102.105, J103.9, J103.41, J103.73, J103.105, J104.9, J104.41, J104.73, J104.105
DB_CTL_09: J101.10, J101.42, J101.74, J101.106, J102.10, J102.42, J102.74, J102.106, J103.10, J103.42, J103.74, J103.106, J104.10, J104.42, J104.74, J104.106
DB_CTL_10: J101.11, J101.43, J101.75, J101.107, J102.11, J102.43, J102.75, J102.107, J103.11, J103.43, J103.75, J103.107, J104.11, J104.43, J104.75, J104.107
DB_CTL_11: J101.12, J101.44, J101.76, J101.108, J102.12, J102.44, J102.76, J102.108, J103.12, J103.44, J103.76, J103.108, J104.12, J104.44, J104.76, J104.108
DB_CTL_12: J101.13, J101.45, J101.77, J101.109, J102.13, J102.45, J102.77, J102.109, J103.13, J103.45, J103.77, J103.109, J104.13, J104.45, J104.77, J104.109
DB_CTL_13: J101.14, J101.46, J101.78, J101.110, J102.14, J102.46, J102.78, J102.110, J103.14, J103.46, J103.78, J103.110, J104.14, J104.46, J104.78, J104.110
DB_CTL_14: J101.15, J101.47, J101.79, J101.111, J102.15, J102.47, J102.79, J102.111, J103.15, J103.47, J103.79, J103.111, J104.15, J104.47, J104.79, J104.111
DB_CTL_15: J101.16, J101.48, J101.80, J101.112, J102.16, J102.48, J102.80, J102.112, J103.16, J103.48, J103.80, J103.112, J104.16, J104.48, J104.80, J104.112
DB_CTL_16: J101.17, J101.49, J101.81, J101.113, J102.17, J102.49, J102.81, J102.113, J103.17, J103.49, J103.81, J103.113, J104.17, J104.49, J104.81, J104.113
DB_CTL_17: J101.18, J101.50, J101.82, J101.114, J102.18, J102.50, J102.82, J102.114, J103.18, J103.50, J103.82, J103.114, J104.18, J104.50, J104.82, J104.114
DB_CTL_18: J101.19, J101.51, J101.83, J101.115, J102.19, J102.51, J102.83, J102.115, J103.19, J103.51, J103.83, J103.115, J104.19, J104.51, J104.83, J104.115
DB_CTL_19: J101.20, J101.52, J101.84, J101.116, J102.20, J102.52, J102.84, J102.116, J103.20, J103.52, J103.84, J103.116, J104.20, J104.52, J104.84, J104.116
DB_CTL_20: J101.21, J101.53, J101.85, J101.117, J102.21, J102.53, J102.85, J102.117, J103.21, J103.53, J103.85, J103.117, J104.21, J104.53, J104.85, J104.117
DB_CTL_21: J101.22, J101.54, J101.86, J101.118, J102.22, J102.54, J102.86, J102.118, J103.22, J103.54, J103.86, J103.118, J104.22, J104.54, J104.86, J104.118
DB_CTL_22: J101.23, J101.55, J101.87, J101.119, J102.23, J102.55, J102.87, J102.119, J103.23, J103.55, J103.87, J103.119, J104.23, J104.55, J104.87, J104.119
DB_CTL_23: J101.24, J101.56, J101.88, J101.120, J102.24, J102.56, J102.88, J102.120, J103.24, J103.56, J103.88, J103.120, J104.24, J104.56, J104.88, J104.120
DB_CTL_24: J101.25, J101.57, J101.89, J102.25, J102.57, J102.89, J103.25, J103.57, J103.89, J104.25, J104.57, J104.89
DB_CTL_25: J101.26, J101.58, J101.90, J102.26, J102.58, J102.90, J103.26, J103.58, J103.90, J104.26, J104.58, J104.90
DB_CTL_26: J101.27, J101.59, J101.91, J102.27, J102.59, J102.91, J103.27, J103.59, J103.91, J104.27, J104.59, J104.91
DB_CTL_27: J101.28, J101.60, J101.92, J102.28, J102.60, J102.92, J103.28, J103.60, J103.92, J104.28, J104.60, J104.92
DB_CTL_28: J101.29, J101.61, J101.93, J102.29, J102.61, J102.93, J103.29, J103.61, J103.93, J104.29, J104.61, J104.93
DB_CTL_29: J101.30, J101.62, J101.94, J102.30, J102.62, J102.94, J103.30, J103.62, J103.94, J104.30, J104.62, J104.94
DB_CTL_30: J101.31, J101.63, J101.95, J102.31, J102.63, J102.95, J103.31, J103.63, J103.95, J104.31, J104.63, J104.95
DB_CTL_31: J101.32, J101.64, J101.96, J102.32, J102.64, J102.96, J103.32, J103.64, J103.96, J104.32, J104.64, J104.96
FAN_PWM_0: J46.1, J46.2, J46.3, J46.4, J46.5, J46.6
FAN_PWM_1: J47.1, J47.2, J47.3, J47.4, J47.5, J47.6
FAN_PWM_2: J48.1, J48.2, J48.3, J48.4, J48.5, J48.6
FAN_PWM_3: J49.1, J49.2, J49.3, J49.4, J49.5, J49.6
FAN_PWM_4: J50.1, J50.2, J50.3, J50.4, J50.5, J50.6
FAN_PWM_5: J51.1, J51.2, J51.3, J51.4, J51.5, J51.6
FAN_PWM_6: J52.1, J52.2, J52.3, J52.4, J52.5, J52.6
GND: C1001.2, C1002.2, C1003.2, C1004.2, C1005.2, C1006.2, C1007.2, C1008.2, C1009.2, C1010.2, C1011.2, C1012.2, C1013.2, C1014.2, C1015.2, C1016.2, C1017.2, C1018.2, C1019.2, C1020.2, C1021.2, C1022.2, C1023.2, C1024.2, C1025.2, C1026.2, C1027.2, C1028.2, C1029.2, C1030.2, C1031.2, C1032.2, C1033.2, C1034.2, C1035.2, C1036.2, C1037.2, C1038.2, C1039.2, C1040.2, C1041.2, C1042.2, C1043.2, C1044.2, C1045.2, C1046.2, C1047.2, C1048.2, C1049.2, C1050.2, C1051.2, C1052.2, C1053.2, C1054.2, C1055.2, C1056.2, C1057.2, C1058.2, C1059.2, C1060.2, C1061.2, C1062.2, C1063.2, C1064.2, C1065.2, C1066.2, C1067.2, C1068.2, C1069.2, C1070.2, C1071.2, C1072.2, C1073.2, C1074.2, C1075.2, C1076.2, C1077.2, C1078.2, C1079.2, C1080.2, C1081.2, C1082.2, C1083.2, C1084.2, C1085.2, C1086.2, C1087.2, C1088.2, C1089.2, C1090.2, C1091.2, C1092.2, C1093.2, C1094.2, C1095.2, C1096.2, MH1.1, MH2.1, MH3.1, MH4.1, MH5.1, MH6.1, MH7.1, MH8.1, U1.1, U1.2, U1.3, U1.4, U1.5, U1.6, U1.7, U1.8, U1.9, U1.10, U1.11, U1.12, U1.13, U1.14, U1.15, U1.16, U1.17, U1.18, U1.19, U1.20, U1.21, U1.22, U1.23, U1.24, U1.25, U1.26, U1.27, U1.28, U1.29, U1.30, U1.31, U1.32, U1.33, U1.34, U1.35, U1.36, U1.37, U1.38, U1.39, U1.40, U1.41, U1.42, U1.43, U1.44, U1.45, U1.46, U1.47, U1.48, U1.49, U1.50, U1.51, U1.52, U1.53, U1.54, U1.55, U1.56, U1.57, U1.58, U1.59, U1.60, U1.61, U1.62, U1.63, U1.64, U1.65, U1.66, U1.67, U1.68, U1.69, U1.70, U1.71, U1.72, U1.73, U1.74, U1.75, U1.76, U1.77, U1.78, U1.79, U1.80, U1.81, U1.82, U1.83, U1.84, U1.85, U1.86, U1.87, U1.88, U1.89, U1.90, U1.91, U1.92, U1.93, U1.95, U1.97, U1.99, U1.101, U1.103, U1.105, U1.107, U1.108, U1.109, U1.110, U1.111, U1.112, U1.113, U1.114, U1.116, U1.118, U1.120, U1.122, U1.124, U1.126, U1.128, U1.129, U1.130, U1.131, U1.132, U1.133, U1.134, U1.135, U1.136, U1.137, U1.139, U1.141, U1.143, U1.145, U1.147, U1.149, U1.151, U1.152, U1.153, U1.154, U1.155, U1.156, U1.157, U1.158, U1.160, U1.170, U1.172, U1.173, U1.174, U1.175, U1.176, U1.177, U1.178, U1.179, U1.180, U1.181, U1.183, U1.193, U1.195, U1.196, U1.197, U1.198, U1.199, U1.200, U1.201, U1.202, U1.204, U1.214, U1.216, U1.217, U1.218, U1.219, U1.220, U1.221, U1.222, U1.223, U1.224, U1.225, U1.227, U1.237, U1.239, U1.240, U1.241, U1.242, U1.243, U1.244, U1.245, U1.246, U1.248, U1.258, U1.260, U1.261, U1.262, U1.263, U1.264, U1.265, U1.266, U1.267, U1.268, U1.269, U1.271, U1.281, U1.283, U1.284, U1.285, U1.286, U1.287, U1.288, U1.289, U1.290, U1.292, U1.302, U1.304, U1.305, U1.306, U1.307, U1.308, U1.309, U1.310, U1.311, U1.312, U1.313, U1.315, U1.325, U1.327, U1.328, U1.329, U1.330, U1.331, U1.332, U1.333, U1.334, U1.336, U1.338, U1.340, U1.342, U1.344, U1.346, U1.348, U1.349, U1.350, U1.351, U1.352, U1.353, U1.354, U1.355, U1.356, U1.357, U1.359, U1.361, U1.363, U1.365, U1.367, U1.369, U1.371, U1.372, U1.373, U1.374, U1.375, U1.376, U1.377, U1.378, U1.380, U1.382, U1.384, U1.386, U1.388, U1.390, U1.392, U1.393, U1.394, U1.395, U1.396, U1.397, U1.398, U1.399, U1.400, U1.401, U1.402, U1.403, U1.404, U1.405, U1.406, U1.407, U1.408, U1.409, U1.410, U1.411, U1.412, U1.413, U1.414, U1.415, U1.416, U1.417, U1.418, U1.419, U1.420, U1.421, U1.422, U1.423, U1.424, U1.425, U1.426, U1.427, U1.428, U1.429, U1.430, U1.431, U1.432, U1.433, U1.434, U1.435, U1.436, U1.437, U1.438, U1.439, U1.440, U1.441, U1.442, U1.443, U1.444, U1.445, U1.446, U1.447, U1.448, U1.449, U1.450, U1.451, U1.452, U1.453, U1.454, U1.455, U1.456, U1.457, U1.458, U1.459, U1.460, U1.461, U1.462, U1.463, U1.464, U1.465, U1.466, U1.467, U1.468, U1.469, U1.470, U1.471, U1.472, U1.473, U1.474, U1.475, U1.476, U1.477, U1.478, U1.479, U1.480, U1.481, U1.482, U1.483, U1.484, U201.GND, U202.GND, U203.GND, U204.GND, U205.GND, U206.GND, U207.GND, U208.GND, U209.GND, U210.GND, U211.GND, U212.GND, U213.GND, U214.GND, U215.GND, U216.GND, U217.GND, U218.GND, U219.GND, U220.GND, U221.GND, U222.GND, U223.GND, U224.GND, U301.GND, U302.GND, U303.GND, U304.GND, U305.GND, U306.GND, U307.GND, U308.GND
MGMT_TX_P: J41.1, J41.2, J41.3, J41.4, J41.5, J41.6, J41.7, J41.8
MGMT_USB_DP: J42.1, J42.2, J42.3, J42.4
PSU_PWR_GOOD_B: J44.25, J44.26, J44.27, J44.28, J44.29, J44.30, J44.31, J44.32, J44.33, J44.34, J44.35, J44.36, J44.37, J44.38, J44.39, J44.40, J44.41, J44.42, J44.43, J44.44, J44.45, J44.46, J44.47, J44.48, J44.49, J44.50, J44.51, J44.52, J44.53, J44.54, J45.25, J45.26, J45.27, J45.28, J45.29, J45.30, J45.31, J45.32, J45.33, J45.34, J45.35, J45.36, J45.37, J45.38, J45.39, J45.40, J45.41, J45.42, J45.43, J45.44, J45.45, J45.46, J45.47, J45.48, J45.49, J45.50, J45.51, J45.52, J45.53, J45.54
V_ASIC_0V85: C1001.1, C1002.1, C1003.1, C1004.1, C1005.1, C1006.1, C1007.1, C1008.1, C1009.1, C1010.1, C1011.1, C1012.1, C1013.1, C1014.1, C1015.1, C1016.1, C1017.1, C1018.1, C1019.1, C1020.1, C1021.1, C1022.1, C1023.1, C1024.1, C1025.1, C1026.1, C1027.1, C1028.1, C1029.1, C1030.1, C1031.1, C1032.1, C1033.1, C1034.1, C1035.1, C1036.1, C1037.1, C1038.1, C1039.1, C1040.1, C1041.1, C1042.1, C1043.1, C1044.1, C1045.1, C1046.1, C1047.1, C1048.1, C1049.1, C1050.1, C1051.1, C1052.1, C1053.1, C1054.1, C1055.1, C1056.1, C1057.1, C1058.1, C1059.1, C1060.1, C1061.1, C1062.1, C1063.1, C1064.1, C1065.1, C1066.1, C1067.1, C1068.1, C1069.1, C1070.1, C1071.1, C1072.1, C1073.1, C1074.1, C1075.1, C1076.1, C1077.1, C1078.1, C1079.1, C1080.1, C1081.1, C1082.1, C1083.1, C1084.1, C1085.1, C1086.1, C1087.1, C1088.1, C1089.1, C1090.1, C1091.1, C1092.1, C1093.1, C1094.1, C1095.1, C1096.1, U1.94, U1.96, U1.98, U1.100, U1.102, U1.104, U1.106, U1.115, U1.117, U1.119, U1.121, U1.123, U1.125, U1.127, U1.138, U1.140, U1.142, U1.144, U1.146, U1.148, U1.150, U1.159, U1.161, U1.162, U1.163, U1.164, U1.165, U1.166, U1.167, U1.168, U1.169, U1.171, U1.182, U1.184, U1.185, U1.186, U1.187, U1.188, U1.189, U1.190, U1.191, U1.192, U1.194, U1.203, U1.205, U1.206, U1.207, U1.208, U1.209, U1.210, U1.211, U1.212, U1.213, U1.215, U1.226, U1.228, U1.229, U1.230, U1.231, U1.232, U1.233, U1.234, U1.235, U1.236, U1.238, U1.247, U1.249, U1.250, U1.251, U1.252, U1.253, U1.254, U1.255, U1.256, U1.257, U1.259, U1.270, U1.272, U1.273, U1.274, U1.275, U1.276, U1.277, U1.278, U1.279, U1.280, U1.282, U1.291, U1.293, U1.294, U1.295, U1.296, U1.297, U1.298, U1.299, U1.300, U1.301, U1.303, U1.314, U1.316, U1.317, U1.318, U1.319, U1.320, U1.321, U1.322, U1.323, U1.324, U1.326, U1.335, U1.337, U1.339, U1.341, U1.343, U1.345, U1.347, U1.358, U1.360, U1.362, U1.364, U1.366, U1.368, U1.370, U1.379, U1.381, U1.383, U1.385, U1.387, U1.389, U1.391, U201.VOUT, U202.VOUT, U203.VOUT, U204.VOUT, U205.VOUT, U206.VOUT, U207.VOUT, U208.VOUT, U209.VOUT, U210.VOUT, U211.VOUT, U212.VOUT, U213.VOUT, U214.VOUT, U215.VOUT, U216.VOUT, U217.VOUT, U218.VOUT, U219.VOUT, U220.VOUT, U221.VOUT, U222.VOUT, U223.VOUT, U224.VOUT
V_OPT_1V2: U301.VOUT, U302.VOUT, U303.VOUT, U304.VOUT, U305.VOUT, U306.VOUT, U307.VOUT, U308.VOUT
V_PSU_12V_A: J44.1, J44.2, J44.3, J44.4, J44.5, J44.6, J44.7, J44.8, J44.9, J44.10, J44.11, J44.12, J44.13, J44.14, J44.15, J44.16, J44.17, J44.18, J44.19, J44.20, J44.21, J44.22, J44.23, J44.24, U201.VIN, U202.VIN, U203.VIN, U204.VIN, U205.VIN, U206.VIN, U207.VIN, U208.VIN, U209.VIN, U210.VIN, U211.VIN, U212.VIN, U213.VIN, U214.VIN, U215.VIN, U216.VIN, U217.VIN, U218.VIN, U219.VIN, U220.VIN, U221.VIN, U222.VIN, U223.VIN, U224.VIN, U301.VIN, U302.VIN, U303.VIN, U304.VIN, U305.VIN, U306.VIN, U307.VIN, U308.VIN
V_PSU_12V_B: J45.1, J45.2, J45.3, J45.4, J45.5, J45.6, J45.7, J45.8, J45.9, J45.10, J45.11, J45.12, J45.13, J45.14, J45.15, J45.16, J45.17, J45.18, J45.19, J45.20, J45.21, J45.22, J45.23, J45.24
